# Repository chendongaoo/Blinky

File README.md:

# Blinky
A mango shaped blinky board that will flash around!

I was able to learn how to apply an image as a pcb edge cut and also enhance more of my pcb design skills.

# PCB Design
This was all done on KiCAD.

- Schematic
- 
- PCB Design
- 

# 3D
This was done on the 3d view option in KiCAD

# BOM (Bill of Materials)
|Amount|Part Name|
|--|--|
|10|LEDS|
|1|NE555P|
|1|Conn 1x2 socket|
|1|Conn 1x1 socket|
|1|1k ohm resistor|
|1|470 ohm resistor|
|1|Potentiometer|
|1|0.01 uF Capacitor|
|1|1 uF Electrolytic capacitor|
|1|CD4017|
|1|PCB|

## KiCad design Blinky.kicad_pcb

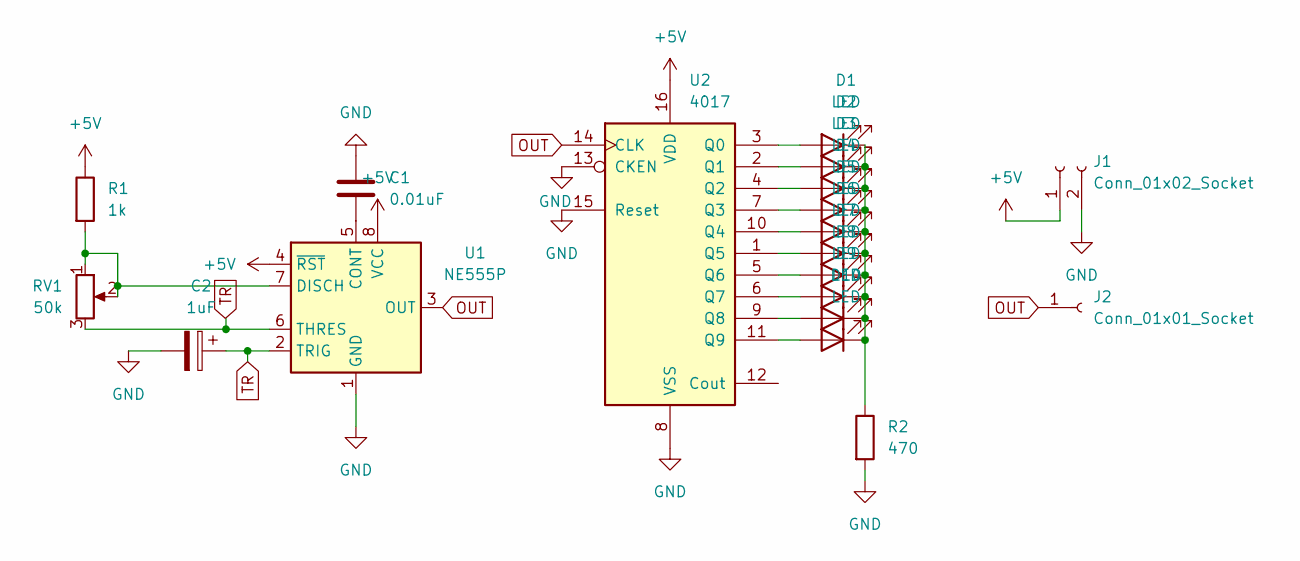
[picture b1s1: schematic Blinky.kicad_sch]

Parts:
C1: 0.01uF; CP_Radial_D5.0mm_P2.00mm
C2: 1uF; C_Disc_D7.5mm_W2.5mm_P5.00mm
D1, D2, D3, D4, D5, D6, D7, D8, D9, D10: LED; LED_D3.0mm
J1: Conn_01x02_Socket; PinHeader_1x02_P2.54mm_Vertical
J2: Conn_01x01_Socket; PinHeader_1x01_P2.54mm_Vertical
R1: 1k; R_Axial_DIN0207_L6.3mm_D2.5mm_P7.62mm_Horizontal
R2: 470; R_Axial_DIN0207_L6.3mm_D2.5mm_P7.62mm_Horizontal
RV1: 50k; Potentiometer_Vishay_T93YA_Vertical
U1: NE555P; DIP-8_W7.62mm
U2: 4017; N16

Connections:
+5V: J1.1, R1.1, U1.4 (~RST), U1.8 (VCC), U2.16 (VDD)
GND: C1.1, C2.2, J1.2, R2.2, U1.1 (GND), U2.8 (VSS), U2.13 (CKEN), U2.15 (Reset)
unnamed: D1.2 (A), U2.3 (Q0)
unnamed: D1.1 (K), D2.1 (K), D3.1 (K), D4.1 (K), D5.1 (K), D6.1 (K), D7.1 (K), D8.1 (K), D9.1 (K), D10.1 (K), R2.1
unnamed: D2.2 (A), U2.2 (Q1)
unnamed: D3.2 (A), U2.4 (Q2)
unnamed: D4.2 (A), U2.7 (Q3)
unnamed: D5.2 (A), U2.10 (Q4)
unnamed: D6.2 (A), U2.1 (Q5)
unnamed: D7.2 (A), U2.5 (Q6)
unnamed: D8.2 (A), U2.6 (Q7)
unnamed: D9.2 (A), U2.9 (Q8)
unnamed: D10.2 (A), U2.11 (Q9)
unnamed: C1.2, U1.5 (CONT)
unnamed: R1.2, RV1.1, RV1.2, U1.7 (DISCH)
unnamed: RV1.3, U1.6 (THRES)
OUT: J2.1 (Pin_1_1), U1.3 (OUT), U2.14 (CLK)
TR: C2.1, U1.2 (TRIG)

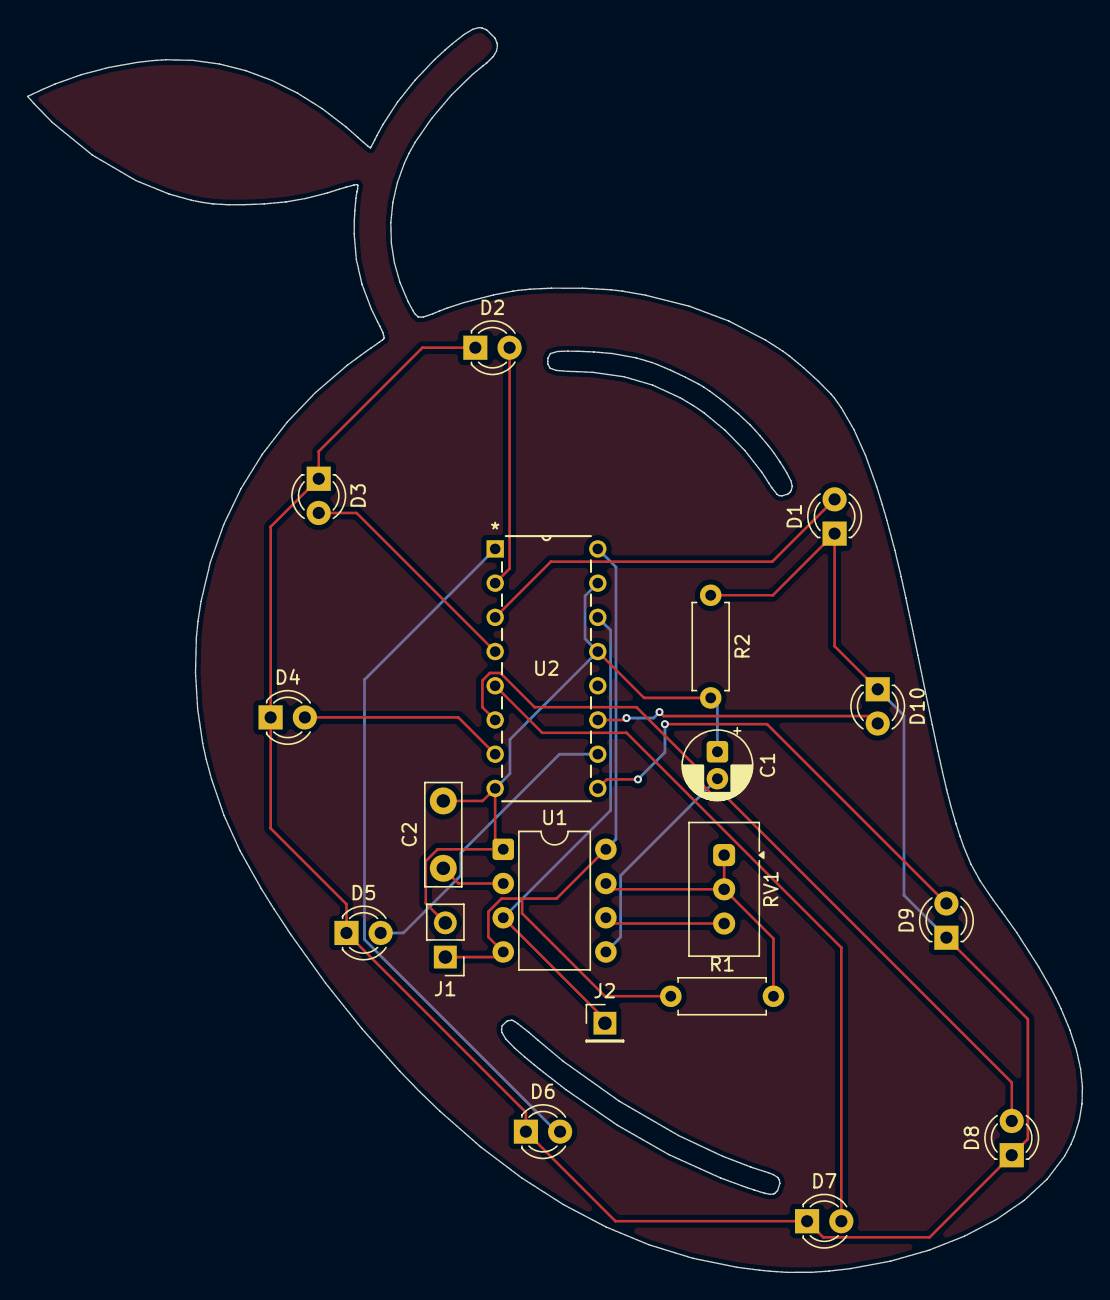
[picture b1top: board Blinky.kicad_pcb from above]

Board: 2 copper layers, 78.3 x 92.4 mm, 19 parts (0 on the bottom side), 18 nets.

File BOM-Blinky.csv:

Comment,Designator,Footprint,LCSC,Quantity
LED,D2,LED_D3.0mm,,1
NE555P,U1,DIP-8_W7.62mm,,1
LED,D6,LED_D3.0mm,,1
LED,D3,LED_D3.0mm,,1
Conn_01x02_Socket,J1,PinHeader_1x02_P2.54mm_Vertical,,1
LED,D1,LED_D3.0mm,,1
LED,D8,LED_D3.0mm,,1
LED,D9,LED_D3.0mm,,1
Conn_01x01_Socket,J2,PinHeader_1x01_P2.54mm_Vertical,,1
4017,U2,N16,,1
LED,D5,LED_D3.0mm,,1
1k,R1,R_Axial_DIN0207_L6.3mm_D2.5mm_P7.62mm_Horizontal,,1
LED,D7,LED_D3.0mm,,1
1uF,C2,C_Disc_D7.5mm_W2.5mm_P5.00mm,,1
LED,D4,LED_D3.0mm,,1
470,R2,R_Axial_DIN0207_L6.3mm_D2.5mm_P7.62mm_Horizontal,,1
LED,D10,LED_D3.0mm,,1
0.01uF,C1,CP_Radial_D5.0mm_P2.00mm,,1
50k,RV1,Potentiometer_Vishay_T93YA_Vertical,,1

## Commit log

2026-06-12 organizing all the files
